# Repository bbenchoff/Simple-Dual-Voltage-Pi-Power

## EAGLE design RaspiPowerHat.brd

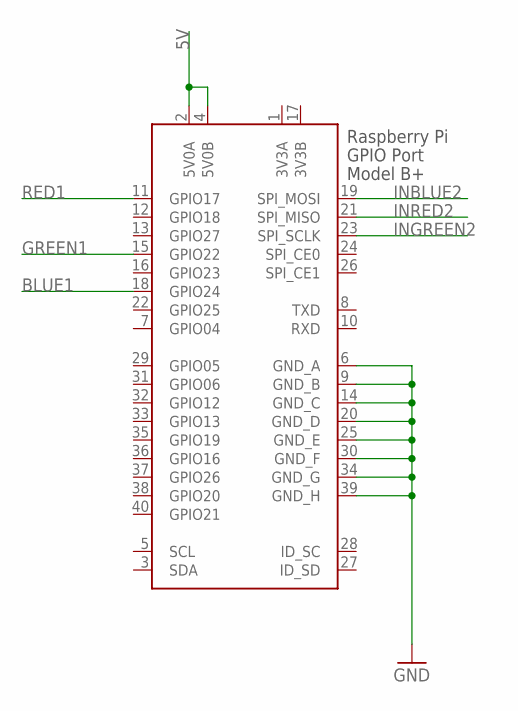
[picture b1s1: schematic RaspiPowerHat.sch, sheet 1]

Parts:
X1: RASPI_GPIO_B+#_PIN; RASPI_GPIO_B+_PIN

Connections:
3V3A: X1.1 (3V3A)
3V3B: X1.17 (3V3B)
5V: X1.2 (5V0A), X1.4 (5V0B); also elsewhere on the board
BLUE1: X1.18 (GPIO24); also elsewhere on the board
GND: X1.6 (GND_A), X1.9 (GND_B), X1.14 (GND_C), X1.20 (GND_D), X1.25 (GND_E), X1.30 (GND_F), X1.34 (GND_G), X1.39 (GND_H); also elsewhere on the board
GREEN1: X1.15 (GPIO22); also elsewhere on the board
INBLUE2: X1.19 (SPI_MOSI); also elsewhere on the board
INGREEN2: X1.23 (SPI_SCLK); also elsewhere on the board
INRED2: X1.21 (SPI_MISO); also elsewhere on the board
RED1: X1.11 (GPIO17); also elsewhere on the board

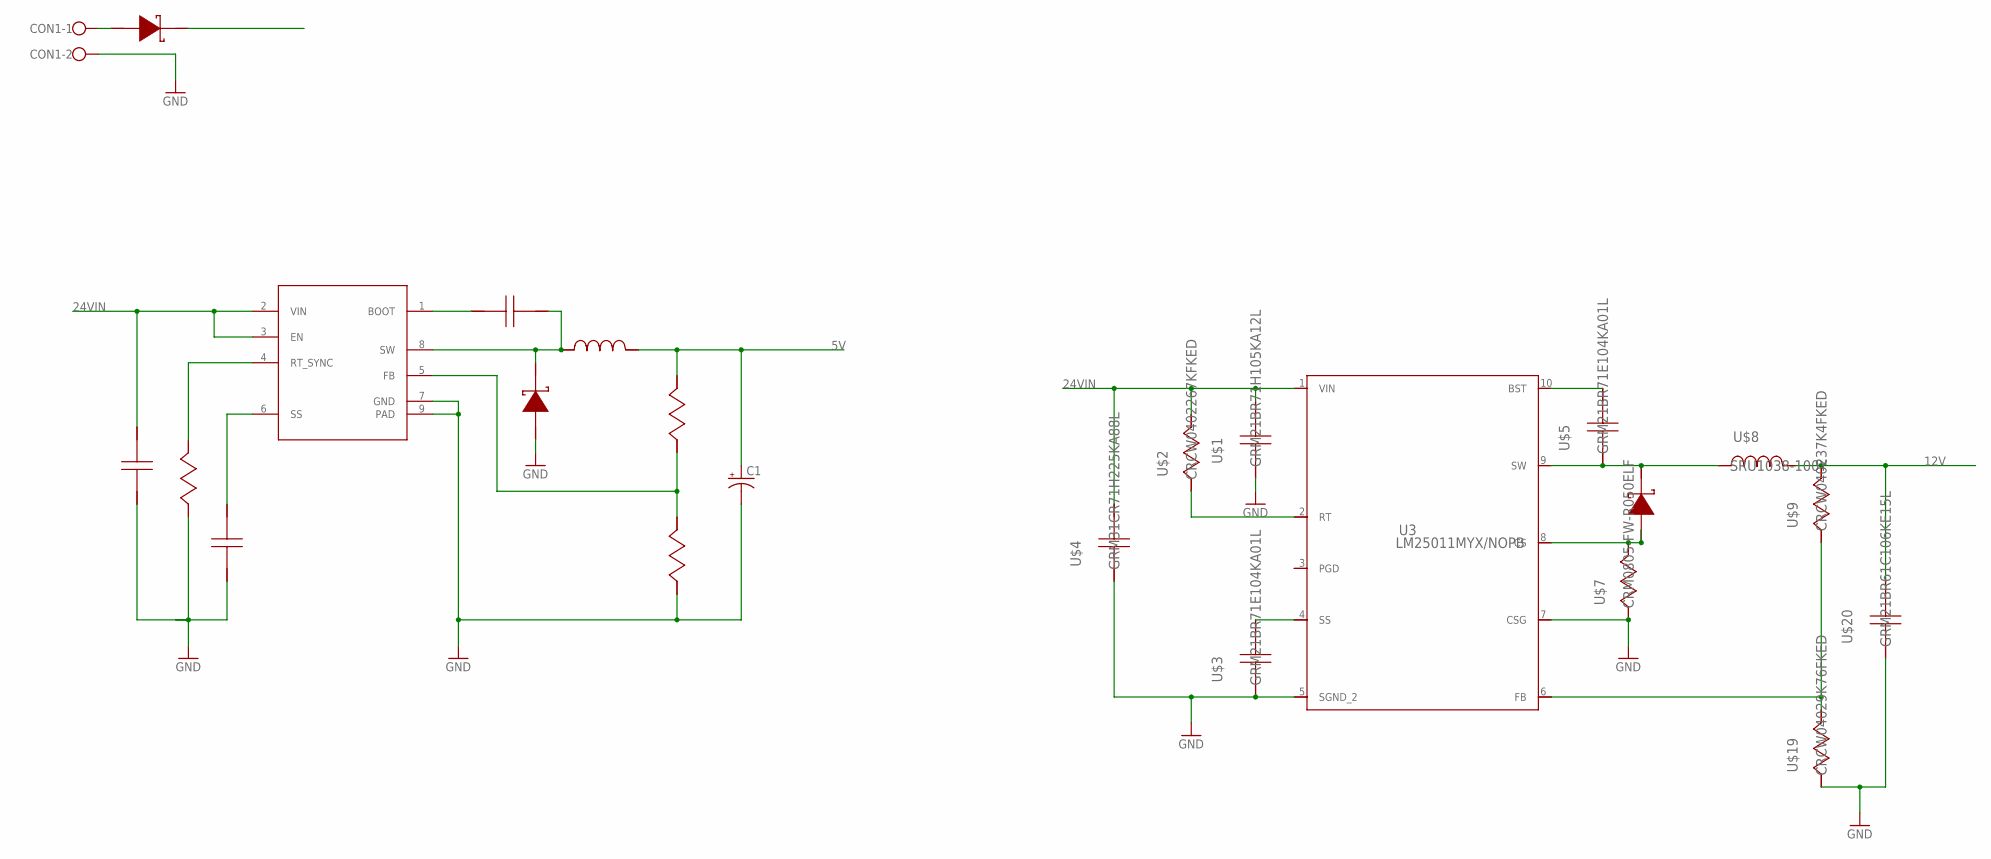
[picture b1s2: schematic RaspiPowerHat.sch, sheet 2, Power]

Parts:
C1: CPOL-USC; PANASONIC_C
CON1: W237-102
U2: Value; DDA0008E_N
U3: LM25011MYX/NOPB; MUC10A
U$1: GRM21BR71H105KA12L; 0805
U$2: CRCW0402267KFKED; 0402
U$3, U$5: GRM21BR71E104KA01L; 0805
U$4, U$18: GRM31CR71H225KA88L; 1206_190
U$6, U$12, U$15: B360A-13-F; SMA
U$7: CRM0805-FW-R050ELF; 0805
U$8: SRU1038-100Y; SRU1038
U$9: CRCW040237K4FKED; 0402
U$10: C0805C104K5RACTU; 0805
U$11: VLP8040T-6R8M; VLP8040
U$13: RC0603FR-0768KL; 0603
U$14: RC0603FR-0712KL; 0603
U$16: GRM155R71C822KA01D; 0402
U$17: CRCW040224K3FKED; 0402
U$19: CRCW04029K76FKED; 0402
U$20: GRM21BR61C106KE15L; 0805

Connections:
5V: C1.+, U$11.2, U$13.1; also elsewhere on the board
12V: U$8.2, U$9.1, U$20.1; also elsewhere on the board
24VIN: U2.2 (VIN), U2.3 (EN), U3.1 (VIN), U$1.1, U$2.1, U$4.1, U$15.1 (K), U$18.1
GND: C1.-, CON1.2, U2.7 (GND), U2.9 (PAD), U3.5 (SGND_2), U3.7 (CSG), U$1.2, U$3.2, U$4.2, U$7.2, U$12.2 (A), U$14.2, U$16.2, U$17.2, U$18.2, U$19.2, U$20.2; also elsewhere on the board
unnamed: U3.2 (RT), U$2.2
unnamed: CON1.1, U$15.2 (A)
unnamed: U3.4 (SS), U$3.1
unnamed: U3.10 (BST), U$5.1
unnamed: U3.9 (SW), U$5.2, U$6.1 (K), U$8.1
unnamed: U2.1 (BOOT), U$10.2
unnamed: U2.8 (SW), U$10.1, U$11.1, U$12.1 (K)
unnamed: U2.5 (FB), U$13.2, U$14.1
unnamed: U2.6 (SS), U$16.1
unnamed: U2.4 (RT_SYNC), U$17.1
unnamed: U3.8 (CS), U$6.2 (A), U$7.1
unnamed: U3.6 (FB), U$9.2, U$19.1

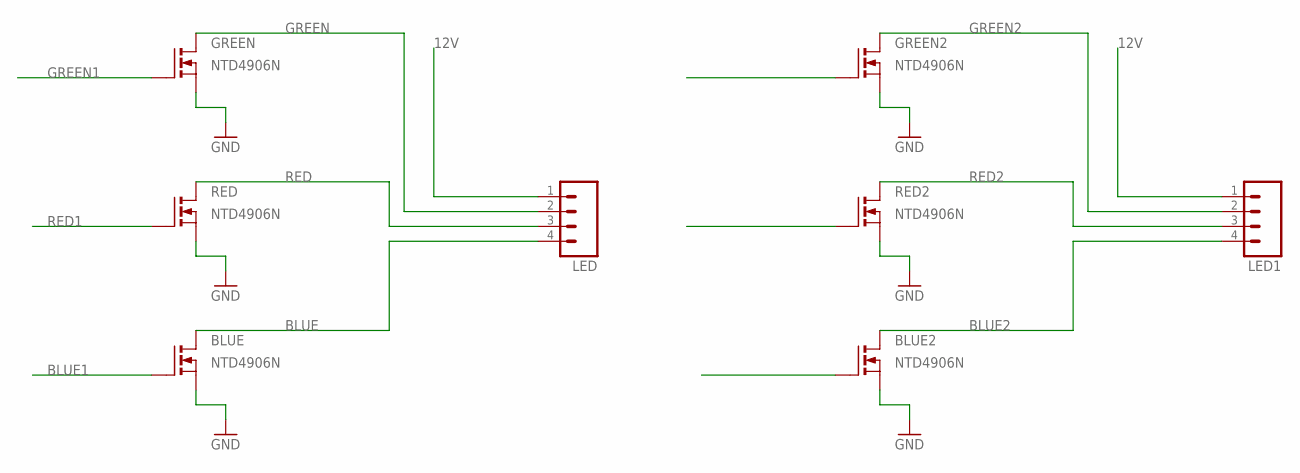
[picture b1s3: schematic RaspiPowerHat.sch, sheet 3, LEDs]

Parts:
BLUE, BLUE2: NTD4906N; D-PAK_TO252AA
GREEN, GREEN2: NTD4906N; D-PAK_TO252AA
LED, LED1: M04JST-PTH-VERT; JST-4-PTH-VERT
RED, RED2: NTD4906N; D-PAK_TO252AA

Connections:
12V: LED.1, LED1.1; also elsewhere on the board
BLUE: BLUE.4 (D), LED.4
BLUE1: BLUE.1 (G); also elsewhere on the board
BLUE2: BLUE2.4 (D), LED1.4
GND: BLUE.3 (SG1), BLUE2.3 (SG1), GREEN.3 (SG1), GREEN2.3 (SG1), RED.3 (SG1), RED2.3 (SG1); also elsewhere on the board
GREEN: GREEN.4 (D), LED.2
GREEN1: GREEN.1 (G); also elsewhere on the board
GREEN2: GREEN2.4 (D), LED1.2
INBLUE2: BLUE2.1 (G); also elsewhere on the board
INGREEN2: GREEN2.1 (G); also elsewhere on the board
INRED2: RED2.1 (G); also elsewhere on the board
RED: LED.3, RED.4 (D)
RED1: RED.1 (G); also elsewhere on the board
RED2: LED1.3, RED2.4 (D)

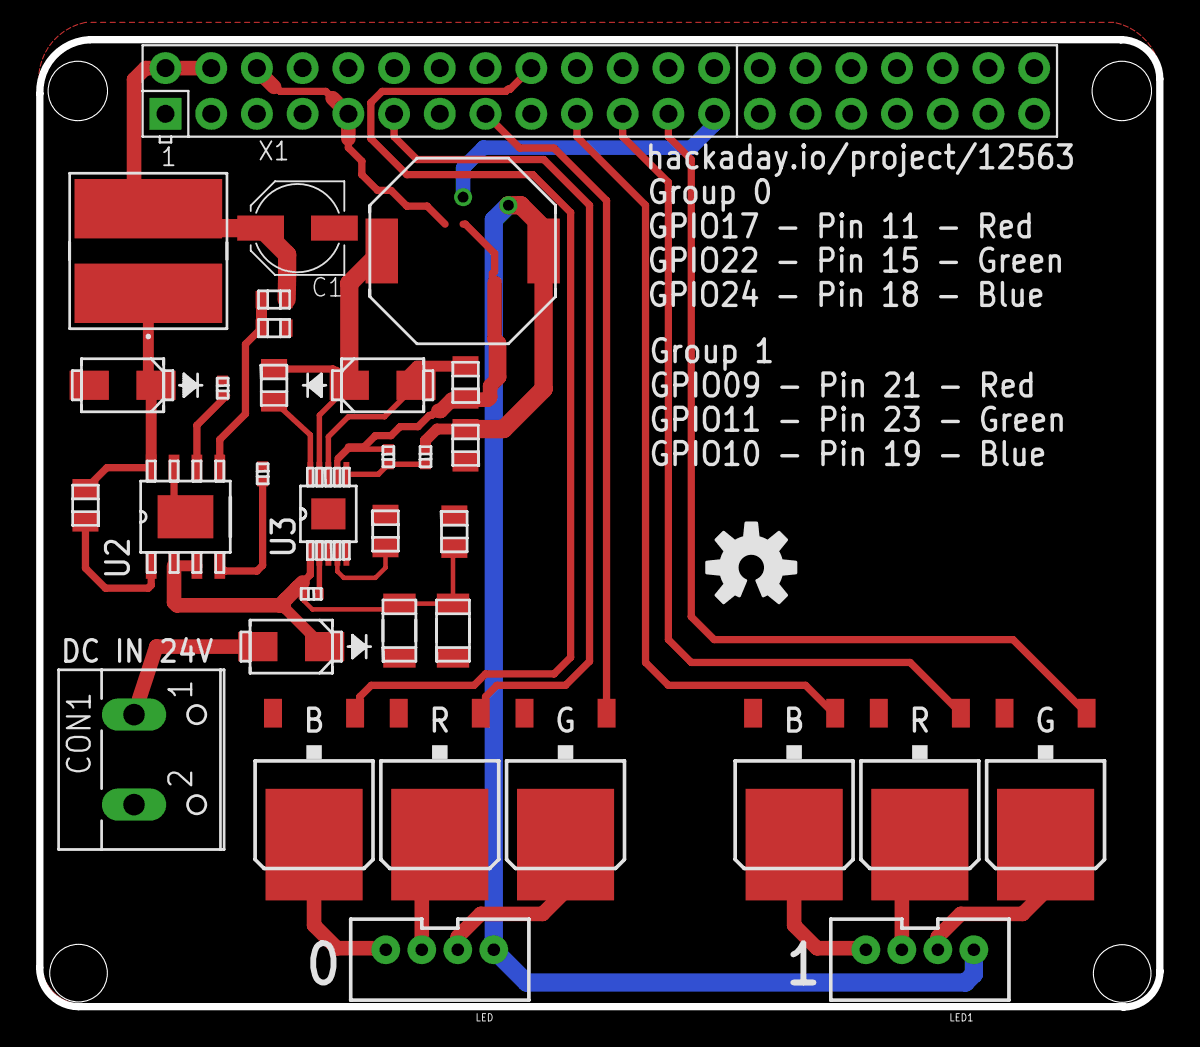
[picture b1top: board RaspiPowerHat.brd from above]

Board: 2 copper layers, 62.2 x 53.7 mm, 34 parts (0 on the bottom side), 28 nets.

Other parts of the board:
U$21: OSHW-LOGO-M

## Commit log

2016-07-07 :tada: Added .gitattributes & .gitignore files
2016-07-07 Board and sch
2016-07-09 Added another RGB channel, fixed footprints

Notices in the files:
parts and their libraries:
SparkFun-Connectors: Licensing: Creative Commons ShareAlike 4.0 International - https://creativecommons.org/licenses/by-sa/4.0
